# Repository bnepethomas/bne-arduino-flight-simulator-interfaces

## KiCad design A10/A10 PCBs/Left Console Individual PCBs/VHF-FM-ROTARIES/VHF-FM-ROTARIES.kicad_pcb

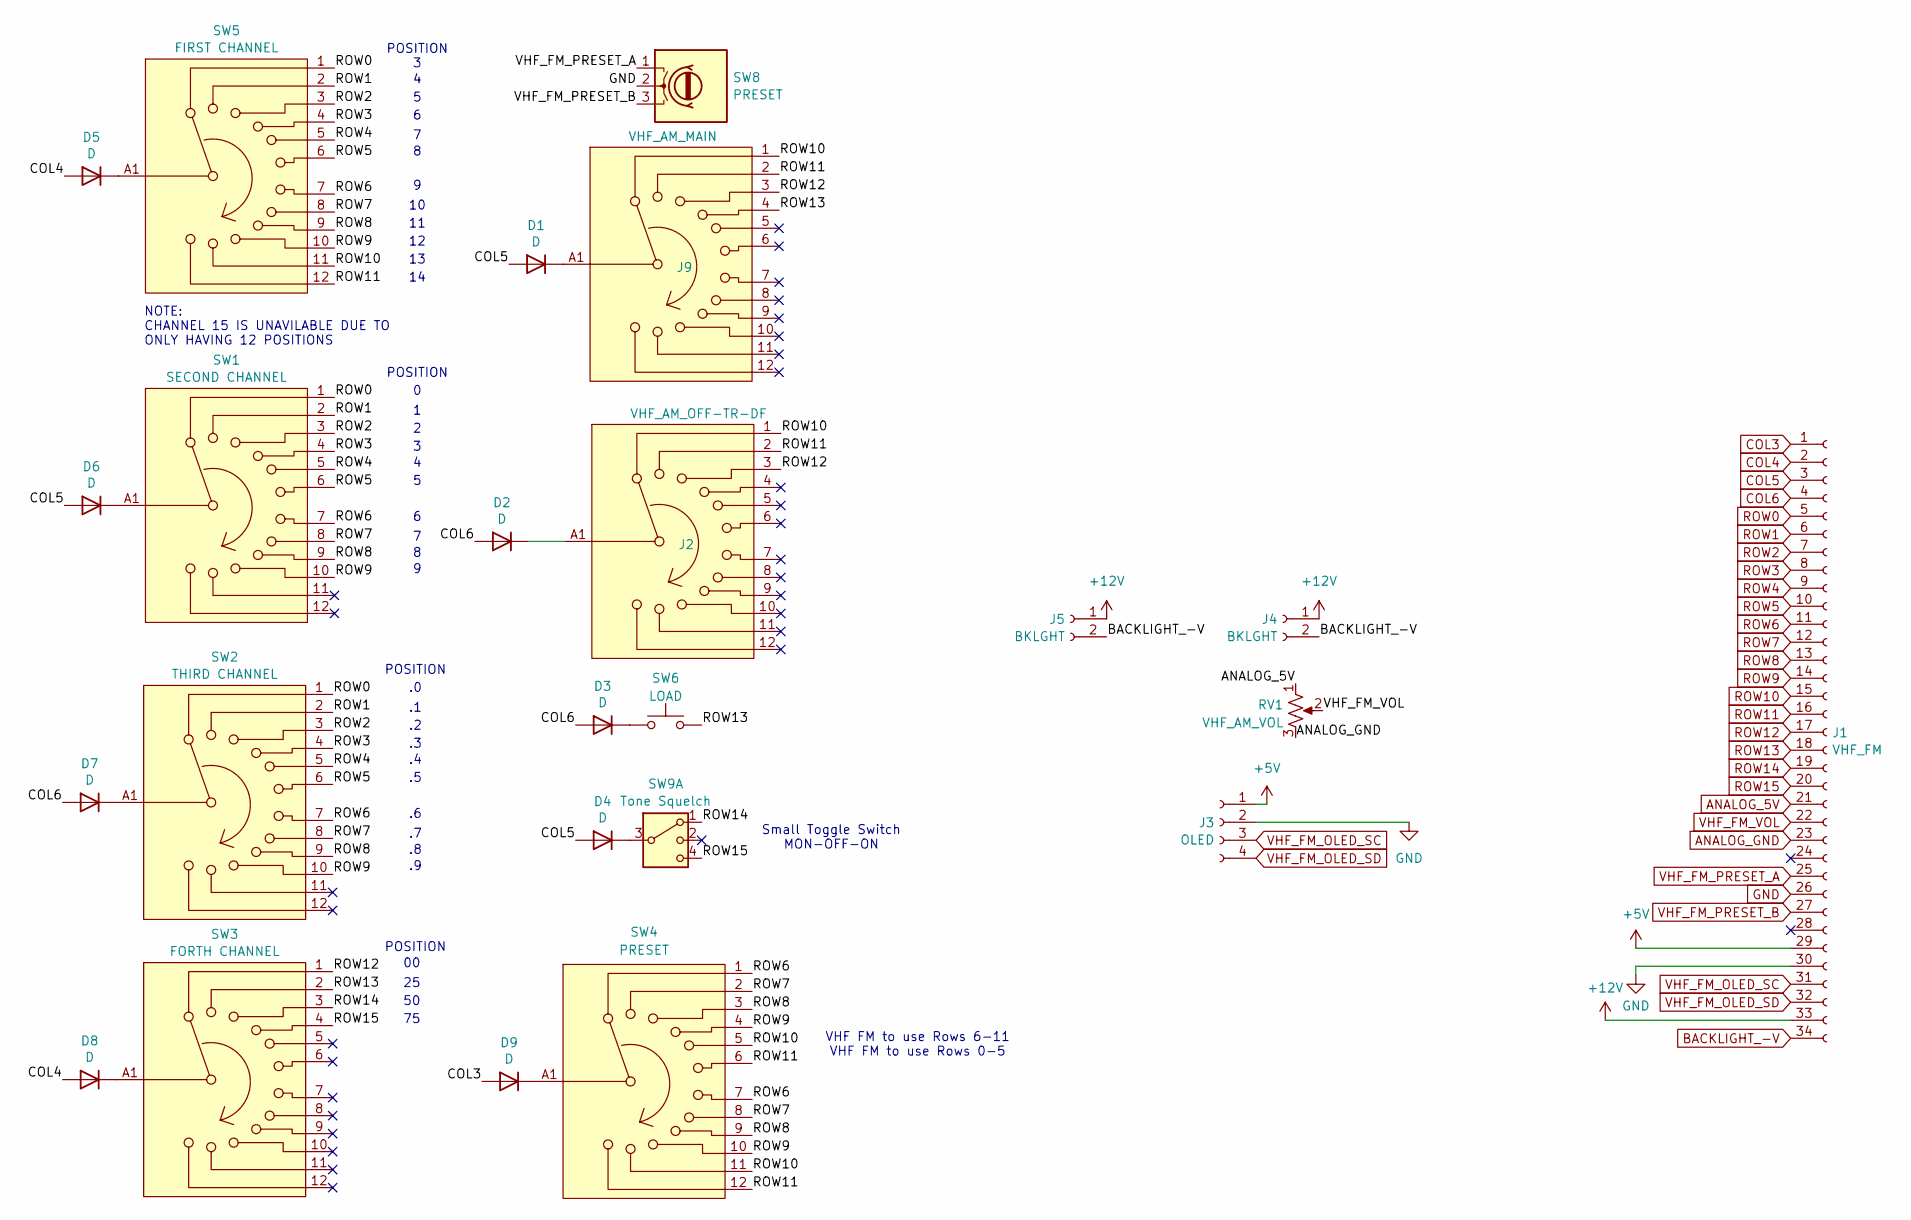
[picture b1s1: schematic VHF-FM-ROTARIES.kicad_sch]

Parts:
D1, D2, D3, D4, D5, D6, D7, D8, D9: D; D_A-405_P7.62mm_Horizontal
J1: VHF_FM; IDC-Header_2x17_P2.54mm_Vertical
J2: VHF_AM_OFF-TR-DF; ALPHA 12 POS
J3: OLED; JST_XH_B4B-XH-A_1x04_P2.50mm_Vertical
J4, J5: BKLGHT; JST_XH_B2B-XH-A_1x02_P2.50mm_Vertical
J9: VHF_AM_MAIN; ALPHA 12 POS
RV1: VHF_AM_VOL; JST_XH_B3B-XH-A_1x03_P2.50mm_Vertical
SW1: SECOND CHANNEL; ALPHA 12 POS
SW2: THIRD CHANNEL; ALPHA 12 POS
SW3: FORTH CHANNEL; ALPHA 12 POS
SW4: PRESET; ALPHA 12 POS
SW5: FIRST CHANNEL; ALPHA 12 POS
SW6: LOAD; JST_XH_B2B-XH-A_1x02_P2.50mm_Vertical
SW8: PRESET; JST_XH_B3B-XH-A_1x03_P2.50mm_Vertical
SW9: Tone Squelch; JST_XH_B3B-XH-A_1x03_P2.50mm_Vertical

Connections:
+5V: J1.29, J3.1
+12V: J1.33, J4.1, J5.1
ANALOG_5V: J1.21, RV1.1
ANALOG_GND: J1.23, RV1.3
BACKLIGHT_-V: J1.34, J4.2, J5.2
COL3: D9.2 (A), J1.1
COL4: D5.2 (A), D8.2 (A), J1.2
COL5: D1.2 (A), D4.2 (A), D6.2 (A), J1.3
COL6: D2.2 (A), D3.2 (A), D7.2 (A), J1.4
GND: J1.26, J1.30, J3.2, SW8.2
unnamed: D1.1 (K), J9.A1
unnamed: D2.1 (K), J2.A1
unnamed: D3.1 (K), SW6.1
unnamed: D4.1 (K), SW9.3
unnamed: D5.1 (K), SW5.A1
unnamed: D6.1 (K), SW1.A1
unnamed: D7.1 (K), SW2.A1
unnamed: D8.1 (K), SW3.A1
unnamed: D9.1 (K), SW4.A1
ROW0: J1.5, SW1.1, SW2.1, SW5.1
ROW1: J1.6, SW1.2, SW2.2, SW5.2
ROW2: J1.7, SW1.3, SW2.3, SW5.3
ROW3: J1.8, SW1.4, SW2.4, SW5.4
ROW4: J1.9, SW1.5, SW2.5, SW5.5
ROW5: J1.10, SW1.6, SW2.6, SW5.6
ROW6: J1.11, SW1.7, SW2.7, SW4.1, SW4.7, SW5.7
ROW7: J1.12, SW1.8, SW2.8, SW4.2, SW4.8, SW5.8
ROW8: J1.13, SW1.9, SW2.9, SW4.3, SW4.9, SW5.9
ROW9: J1.14, SW1.10, SW2.10, SW4.4, SW4.10, SW5.10
ROW10: J1.15, J2.1, J9.1, SW4.5, SW4.11, SW5.11
ROW11: J1.16, J2.2, J9.2, SW4.6, SW4.12, SW5.12
ROW12: J1.17, J2.3, J9.3, SW3.1
ROW13: J1.18, J9.4, SW3.2, SW6.2
ROW14: J1.19, SW3.3, SW9.1
ROW15: J1.20, SW3.4, SW9.4
VHF_FM_OLED_SC: J1.31, J3.3
VHF_FM_OLED_SD: J1.32, J3.4
VHF_FM_PRESET_A: J1.25, SW8.1
VHF_FM_PRESET_B: J1.27, SW8.3
VHF_FM_VOL: J1.22, RV1.2

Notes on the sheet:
VHF FM to use Rows 6-11 VHF FM to use Rows 0-5
NOTE: CHANNEL 15 IS UNAVILABLE DUE TO ONLY HAVING 12 POSITIONS
POSITION
Small Toggle Switch MON-OFF-ON

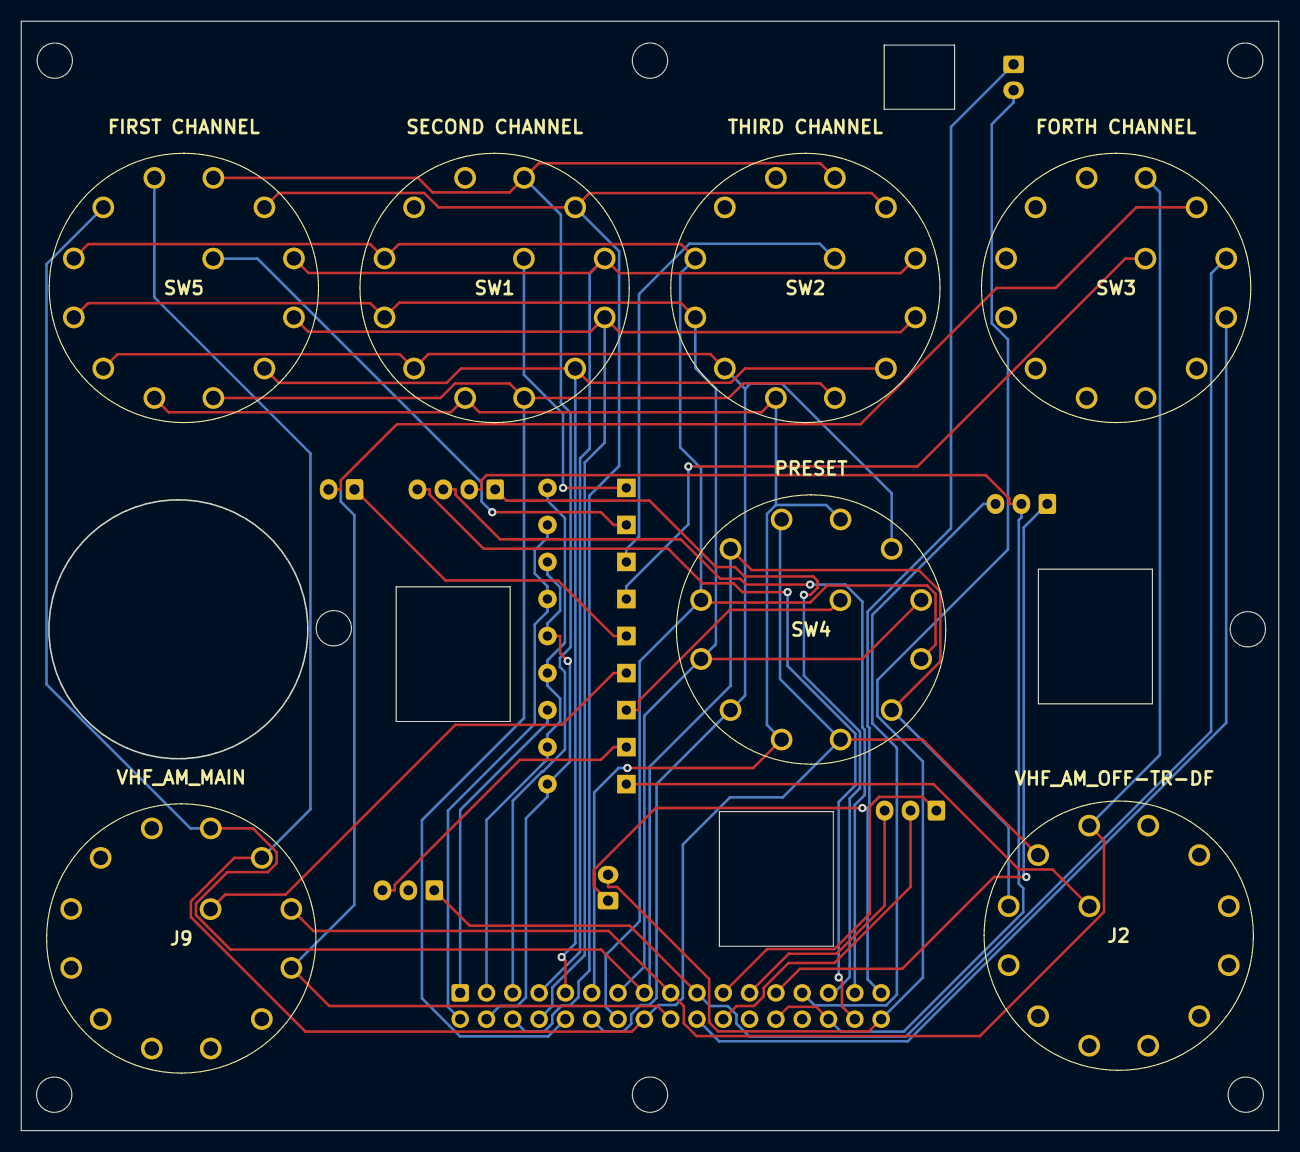
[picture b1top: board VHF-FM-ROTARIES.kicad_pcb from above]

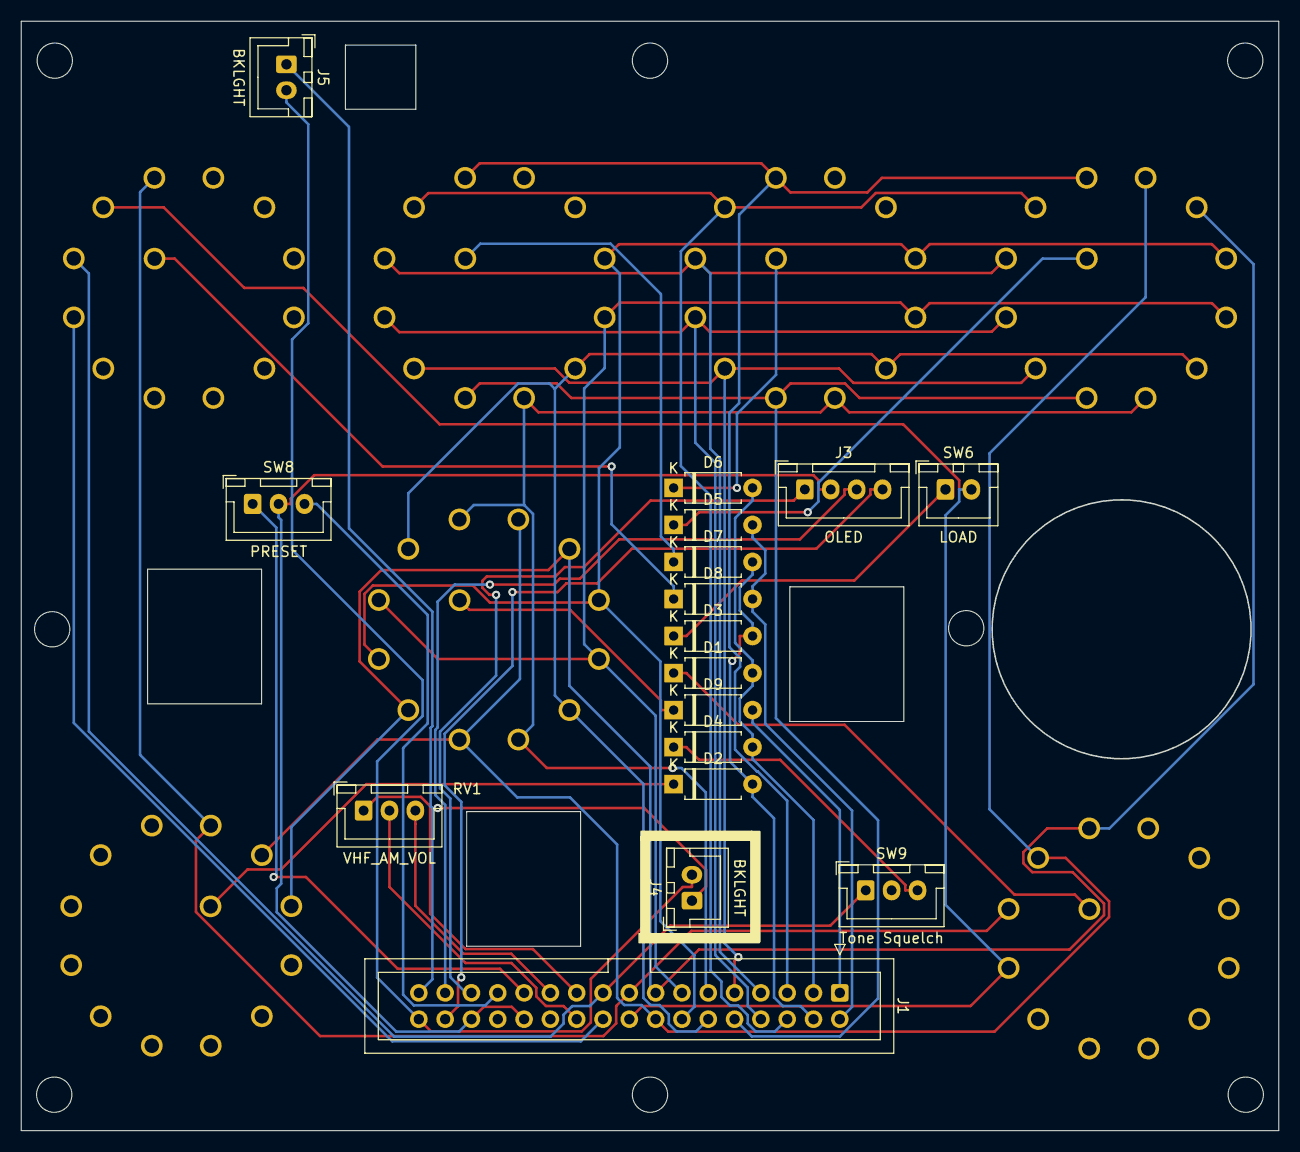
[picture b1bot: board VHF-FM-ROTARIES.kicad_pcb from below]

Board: 2 copper layers, 121.4 x 107.1 mm, 24 parts (17 on the bottom side), 40 nets.

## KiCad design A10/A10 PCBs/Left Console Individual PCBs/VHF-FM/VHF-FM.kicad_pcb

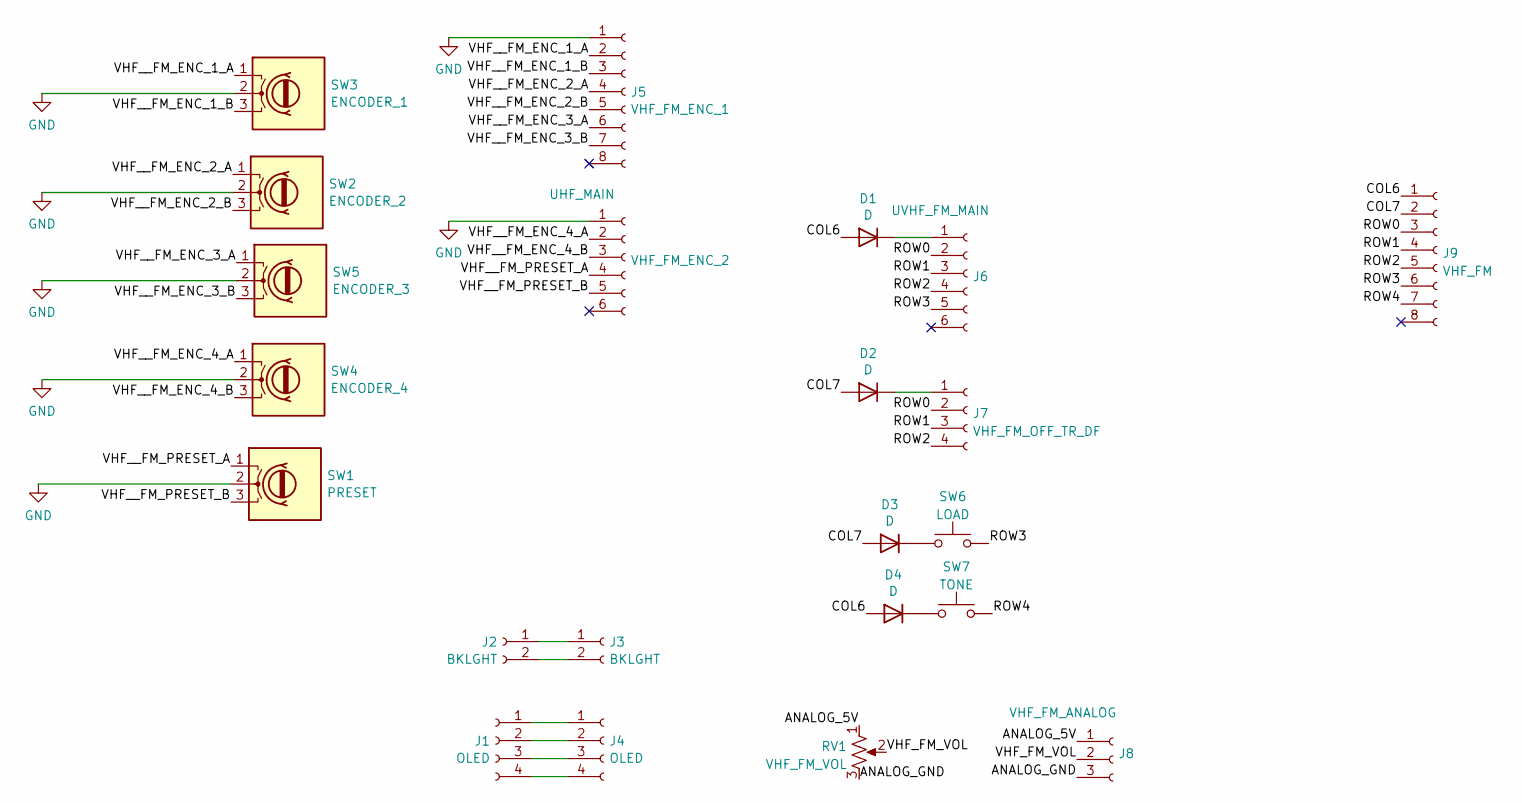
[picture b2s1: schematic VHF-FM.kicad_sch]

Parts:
D1, D2, D3, D4: D; D_A-405_P7.62mm_Horizontal
J1, J4: OLED; Molex_KK-254_AE-6410-04A_1x04_P2.54mm_Vertical
J2, J3: BKLGHT; Molex_KK-254_AE-6410-02A_1x02_P2.54mm_Vertical
J5: VHF_FM_ENC_1; Molex_KK-254_AE-6410-08A_1x08_P2.54mm_Vertical
J6: UVHF_FM_MAIN; Molex_KK-254_AE-6410-06A_1x06_P2.54mm_Vertical
J7: VHF_FM_OFF_TR_DF; Molex_KK-254_AE-6410-04A_1x04_P2.54mm_Vertical
J8: VHF_FM_ANALOG; Molex_KK-254_AE-6410-03A_1x03_P2.54mm_Vertical
J9: VHF_FM; Molex_KK-254_AE-6410-06A_1x06_P2.54mm_Vertical
RV1: VHF_FM_VOL; Molex_KK-254_AE-6410-03A_1x03_P2.54mm_Vertical
SW1: PRESET; Molex_KK-254_AE-6410-03A_1x03_P2.54mm_Vertical
SW2: ENCODER_2; Molex_KK-254_AE-6410-03A_1x03_P2.54mm_Vertical
SW3: ENCODER_1; Molex_KK-254_AE-6410-03A_1x03_P2.54mm_Vertical
SW4: ENCODER_4; Molex_KK-254_AE-6410-03A_1x03_P2.54mm_Vertical
SW5: ENCODER_3; Molex_KK-254_AE-6410-03A_1x03_P2.54mm_Vertical
SW6: LOAD; Molex_KK-254_AE-6410-02A_1x02_P2.54mm_Vertical
SW7: TONE; Molex_KK-254_AE-6410-02A_1x02_P2.54mm_Vertical
VHF_FM_ENC_2: UHF_MAIN; Molex_KK-254_AE-6410-06A_1x06_P2.54mm_Vertical

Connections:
/ANALOG_5V: J8.1, RV1.1
/ANALOG_GND: J8.3, RV1.3
/COL6: D1.2 (A), D4.2 (A), J9.1
/COL7: D2.2 (A), D3.2 (A), J9.2
/ROW0: J6.2, J7.2, J9.3
/ROW1: J6.3, J7.3, J9.4
/ROW2: J6.4, J7.4, J9.5
/ROW3: J6.5, J9.6, SW6.2
/ROW4: J9.7, SW7.2
/VHF_FM_VOL: J8.2, RV1.2
/VHF__FM_ENC_1_A: J5.2, SW3.1
/VHF__FM_ENC_1_B: J5.3, SW3.3
/VHF__FM_ENC_2_A: J5.4, SW2.1
/VHF__FM_ENC_2_B: J5.5, SW2.3
/VHF__FM_ENC_3_A: J5.6, SW5.1
/VHF__FM_ENC_3_B: J5.7, SW5.3
/VHF__FM_ENC_4_A: SW4.1, VHF_FM_ENC_2.2
/VHF__FM_ENC_4_B: SW4.3, VHF_FM_ENC_2.3
/VHF__FM_PRESET_A: SW1.1, VHF_FM_ENC_2.4
/VHF__FM_PRESET_B: SW1.3, VHF_FM_ENC_2.5
GND: J5.1, SW1.2, SW2.2, SW3.2, SW4.2, SW5.2, VHF_FM_ENC_2.1
unnamed: D1.1 (K), J6.1
unnamed: D2.1 (K), J7.1
unnamed: D3.1 (K), SW6.1
unnamed: D4.1 (K), SW7.1
unnamed: J1.1, J4.1
unnamed: J1.2, J4.2
unnamed: J1.3, J4.3
unnamed: J1.4, J4.4
unnamed: J2.1, J3.1
unnamed: J2.2, J3.2

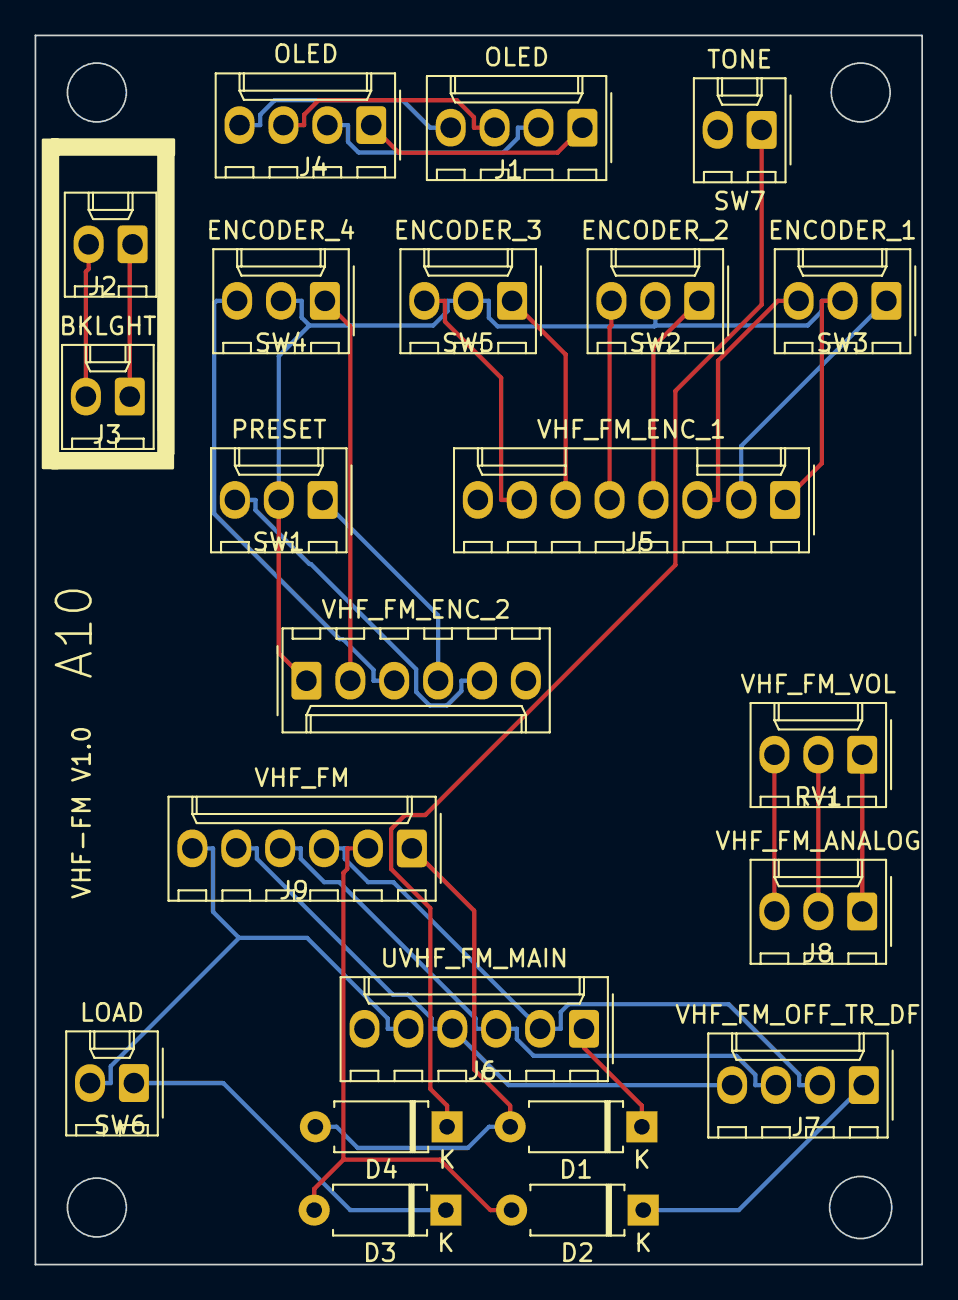
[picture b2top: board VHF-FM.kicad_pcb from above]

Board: 2 copper layers, 51.3 x 71.1 mm, 22 parts (0 on the bottom side), 30 nets.

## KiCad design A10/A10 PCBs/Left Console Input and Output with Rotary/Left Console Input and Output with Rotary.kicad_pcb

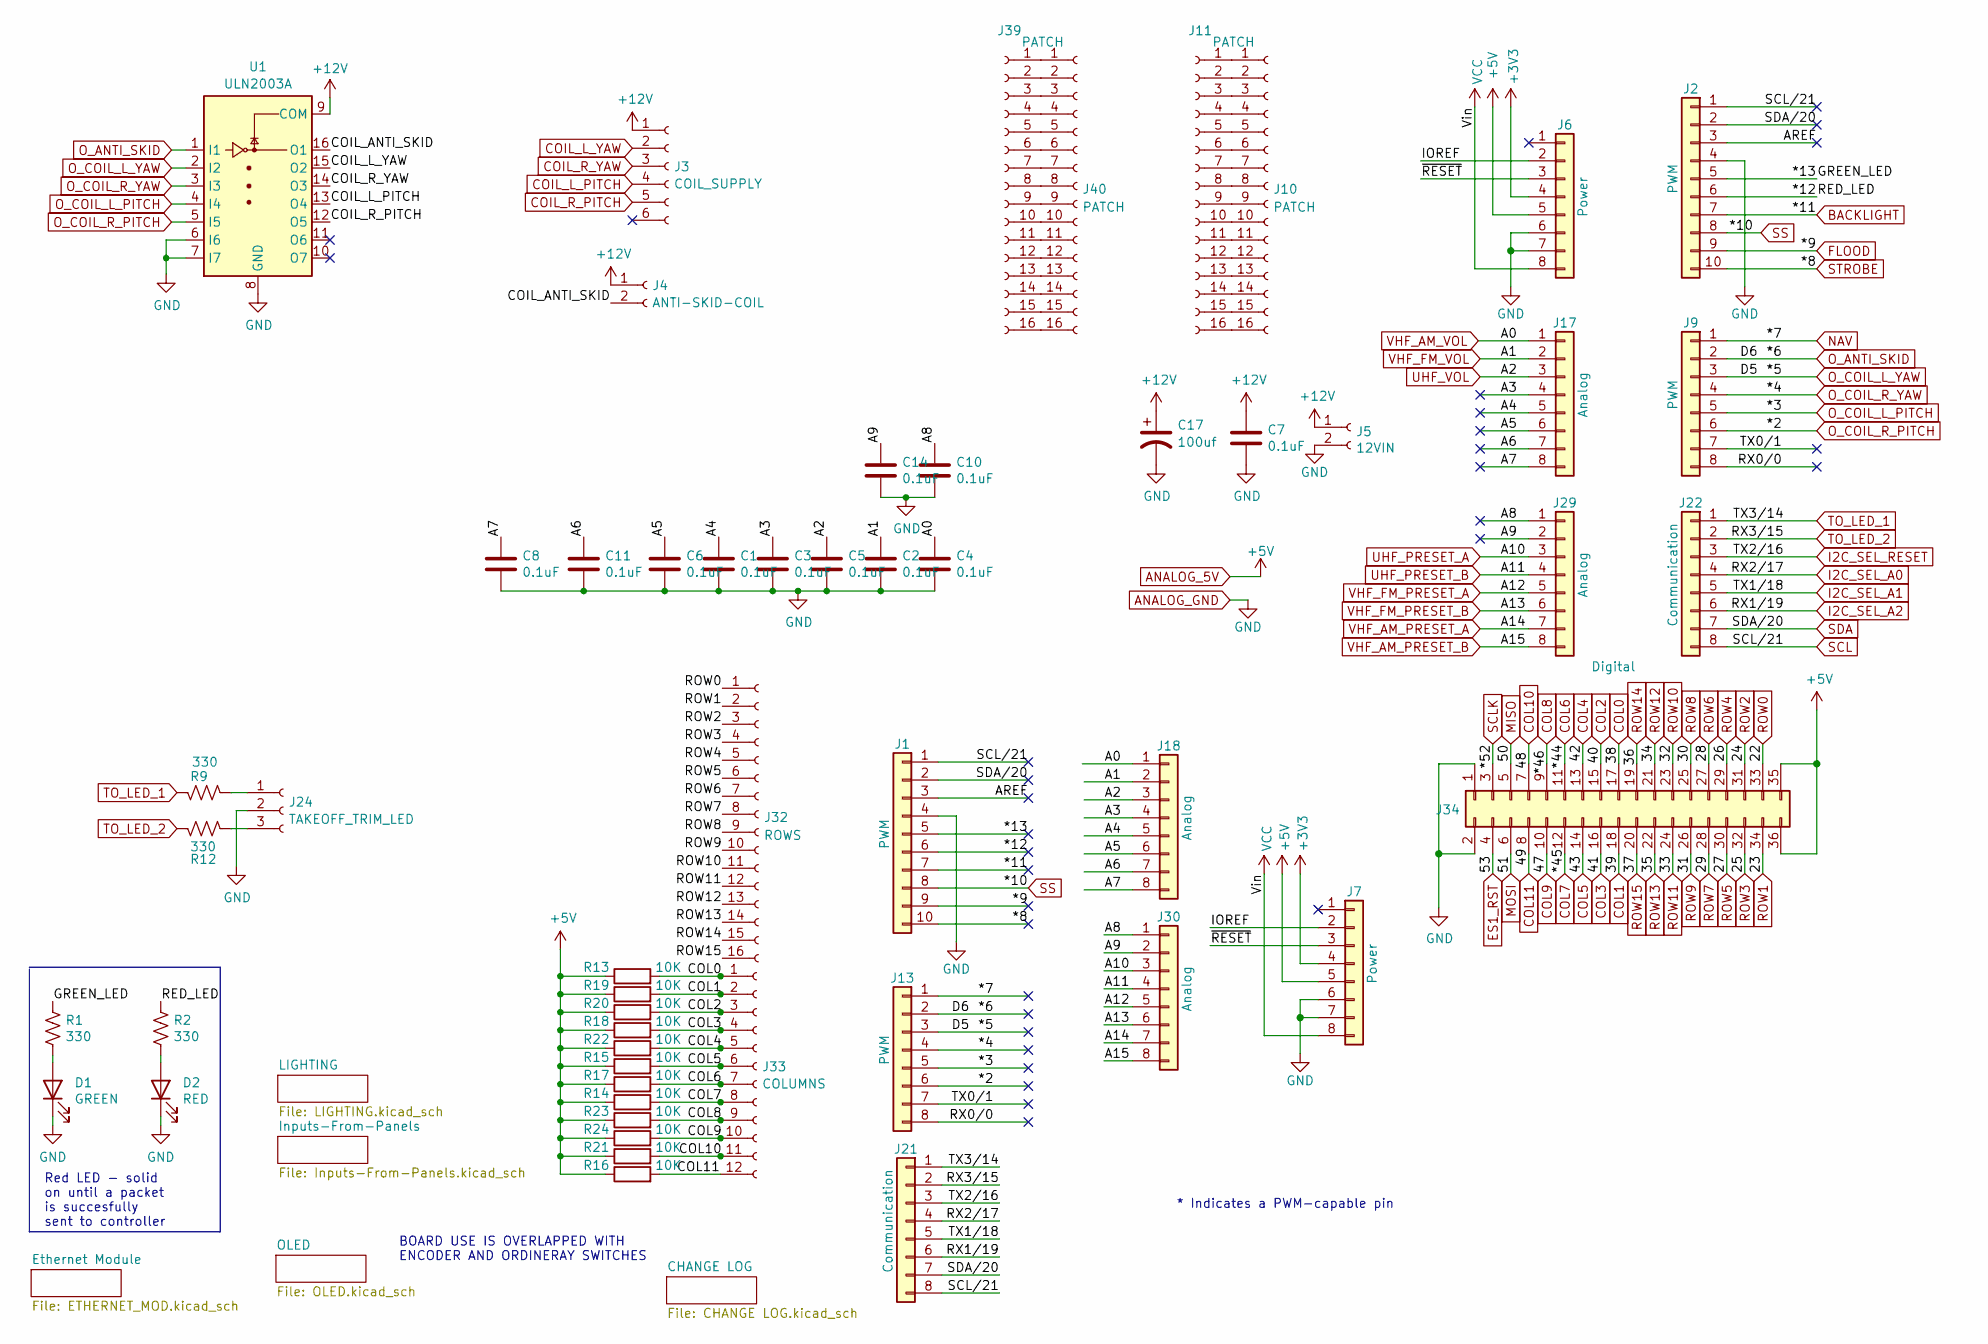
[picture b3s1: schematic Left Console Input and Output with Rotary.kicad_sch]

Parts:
C1, C2, C3, C4, C5, C6, C8, C10, C11, C14: 0.1uF; C_Disc_D6.0mm_W2.5mm_P5.00mm
C7: 0.1uF; C_Disc_D4.3mm_W1.9mm_P5.00mm
C17: 100uf; C_Radial_D6.3mm_H5.0mm_P2.50mm
D1: GREEN; LED_D3.0mm
D2: RED; LED_D3.0mm
J1, J2: PWM; PinSocket_1x10_P2.54mm_Vertical
J3: COIL_SUPPLY; Molex_KK-254_AE-6410-06A_1x06_P2.54mm_Vertical
J4: ANTI-SKID-COIL; Molex_KK-254_AE-6410-02A_1x02_P2.54mm_Vertical
J5: 12VIN; BarrelJack_Horizontal
J6, J7: Power; PinSocket_1x08_P2.54mm_Vertical
J9, J13: PWM; PinSocket_1x08_P2.54mm_Vertical
J10, J11, J39, J40: PATCH; PinHeader_1x16_P2.54mm_Vertical
J17, J18, J29, J30: Analog; PinSocket_1x08_P2.54mm_Vertical
J21, J22: Communication; PinSocket_1x08_P2.54mm_Vertical
J24: TAKEOFF_TRIM_LED; Molex_KK-254_AE-6410-03A_1x03_P2.54mm_Vertical
J32: ROWS; PinHeader_1x16_P2.54mm_Vertical
J33: COLUMNS; PinHeader_1x12_P2.54mm_Vertical
J34: Digital; PinSocket_2x18_P2.54mm_Vertical
R1, R2, R9, R12: 330; R_Axial_DIN0204_L3.6mm_D1.6mm_P2.54mm_Vertical
R13, R14, R15, R16, R17, R18, R19, R20, R21, R22, R23, R24: 10K; R_Axial_DIN0204_L3.6mm_D1.6mm_P2.54mm_Vertical
U1: ULN2003A; DIP-16_W7.62mm_LongPads

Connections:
+3V3: J6.4, J7.4; also elsewhere on the board
+12V: C7.1, C17.1, J3.1, J4.1, J5.1, U1.9 (COM); also elsewhere on the board
/*12: J1.6, J2.6, R2.1
/*13: J1.5, J2.5, R1.1
/A3: C3.1, J17.4, J18.4
/A4: C1.1, J17.5, J18.5
/A5: C6.1, J17.6, J18.6
/A6: C11.1, J17.7, J18.7
/A7: C8.1, J17.8, J18.8
/A8: C10.1, J29.1, J30.1
/A9: C14.1, J29.2, J30.2
/AREF: J1.3, J2.3
/COIL_ANTI_SKID: J4.2, U1.16 (O1)
/IOREF: J6.2, J7.2
/~RESET: J6.3, J7.3
BACKLIGHT: J1.7, J2.7; also elsewhere on the board
COIL_L_PITCH: J3.4, U1.13 (O4)
COIL_L_YAW: J3.2, U1.15 (O2)
COIL_R_PITCH: J3.5, U1.12 (O5)
COIL_R_YAW: J3.3, U1.14 (O3)
COL0: J33.1, J34.17, R13.2; also elsewhere on the board
COL1: J33.2, J34.18, R19.2; also elsewhere on the board
COL2: J33.3, J34.15, R20.2; also elsewhere on the board
COL3: J33.4, J34.16, R18.2; also elsewhere on the board
COL4: J33.5, J34.13, R22.2; also elsewhere on the board
COL5: J33.6, J34.14, R15.2; also elsewhere on the board
COL6: J33.7, J34.11, R17.2; also elsewhere on the board
COL7: J33.8, J34.12, R14.2; also elsewhere on the board
COL8: J33.9, J34.9, R23.2; also elsewhere on the board
COL9: J33.10, J34.10, R24.2; also elsewhere on the board
COL10: J33.11, J34.7, R21.2; also elsewhere on the board
COL11: J33.12, J34.8, R16.2; also elsewhere on the board
ES1_RST: J34.4; also elsewhere on the board
FLOOD: J1.9, J2.9; also elsewhere on the board
I2C_SEL_A0: J21.4, J22.4; also elsewhere on the board
I2C_SEL_A1: J21.5, J22.5; also elsewhere on the board
I2C_SEL_A2: J21.6, J22.6; also elsewhere on the board
I2C_SEL_RESET: J21.3, J22.3; also elsewhere on the board
MISO: J34.5; also elsewhere on the board
MOSI: J34.6; also elsewhere on the board
NAV: J9.1, J13.1; also elsewhere on the board
unnamed: D1.2 (A), R1.2
unnamed: D2.2 (A), R2.2
unnamed: J10.1, J11.1
unnamed: J10.2, J11.2
unnamed: J10.3, J11.3
unnamed: J10.4, J11.4
unnamed: J10.5, J11.5
unnamed: J10.6, J11.6
unnamed: J10.7, J11.7
unnamed: J10.8, J11.8
unnamed: J10.9, J11.9
unnamed: J10.10, J11.10
unnamed: J10.11, J11.11
unnamed: J10.12, J11.12
unnamed: J10.13, J11.13
unnamed: J10.14, J11.14
unnamed: J10.15, J11.15
unnamed: J10.16, J11.16
unnamed: J24.1, R9.1
unnamed: J24.3, R12.1
unnamed: J39.1, J40.1
unnamed: J39.2, J40.2
unnamed: J39.3, J40.3
unnamed: J39.4, J40.4
unnamed: J39.5, J40.5
unnamed: J39.6, J40.6
unnamed: J39.7, J40.7
unnamed: J39.8, J40.8
unnamed: J39.9, J40.9
unnamed: J39.10, J40.10
unnamed: J39.11, J40.11
unnamed: J39.12, J40.12
unnamed: J39.13, J40.13
unnamed: J39.14, J40.14
unnamed: J39.15, J40.15
unnamed: J39.16, J40.16
O_ANTI_SKID: J9.2, J13.2, U1.1 (I1)
O_COIL_L_PITCH: J9.5, J13.5, U1.4 (I4)
O_COIL_L_YAW: J9.3, J13.3, U1.2 (I2)
O_COIL_R_PITCH: J9.6, J13.6, U1.5 (I5)
O_COIL_R_YAW: J9.4, J13.4, U1.3 (I3)
ROW0: J32.1, J34.33; also elsewhere on the board
ROW1: J32.2, J34.34; also elsewhere on the board
ROW2: J32.3, J34.31; also elsewhere on the board
ROW3: J32.4, J34.32; also elsewhere on the board
ROW4: J32.5, J34.29; also elsewhere on the board
ROW5: J32.6, J34.30; also elsewhere on the board
ROW6: J32.7, J34.27; also elsewhere on the board
ROW7: J32.8, J34.28; also elsewhere on the board
ROW8: J32.9, J34.25; also elsewhere on the board
ROW9: J32.10, J34.26; also elsewhere on the board
ROW10: J32.11, J34.23; also elsewhere on the board
ROW11: J32.12, J34.24; also elsewhere on the board
ROW12: J32.13, J34.21; also elsewhere on the board
ROW13: J32.14, J34.22; also elsewhere on the board
ROW14: J32.15, J34.19; also elsewhere on the board
ROW15: J32.16, J34.20; also elsewhere on the board
SCL: J1.1, J2.1, J21.8, J22.8; also elsewhere on the board
SCLK: J34.3; also elsewhere on the board
SDA: J1.2, J2.2, J21.7, J22.7; also elsewhere on the board
SS: J1.8, J2.8; also elsewhere on the board
STROBE: J1.10, J2.10; also elsewhere on the board
UHF_PRESET_A: J29.3, J30.3; also elsewhere on the board
UHF_PRESET_B: J29.4, J30.4; also elsewhere on the board
UHF_VOL: C5.1, J17.3, J18.3; also elsewhere on the board
VCC: J6.8, J7.8
VHF_AM_PRESET_A: J29.7, J30.7; also elsewhere on the board
VHF_AM_PRESET_B: J29.8, J30.8; also elsewhere on the board
VHF_AM_VOL: C4.1, J17.1, J18.1; also elsewhere on the board
VHF_FM_PRESET_A: J29.5, J30.5; also elsewhere on the board
VHF_FM_PRESET_B: J29.6, J30.6; also elsewhere on the board
VHF_FM_VOL: C2.1, J17.2, J18.2; also elsewhere on the board

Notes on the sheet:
BOARD USE IS OVERLAPPED WITH ENCODER AND ORDINERAY SWITCHES
Red LED - solid on until a packet is succesfully sent to controller
* Indicates a PWM-capable pin

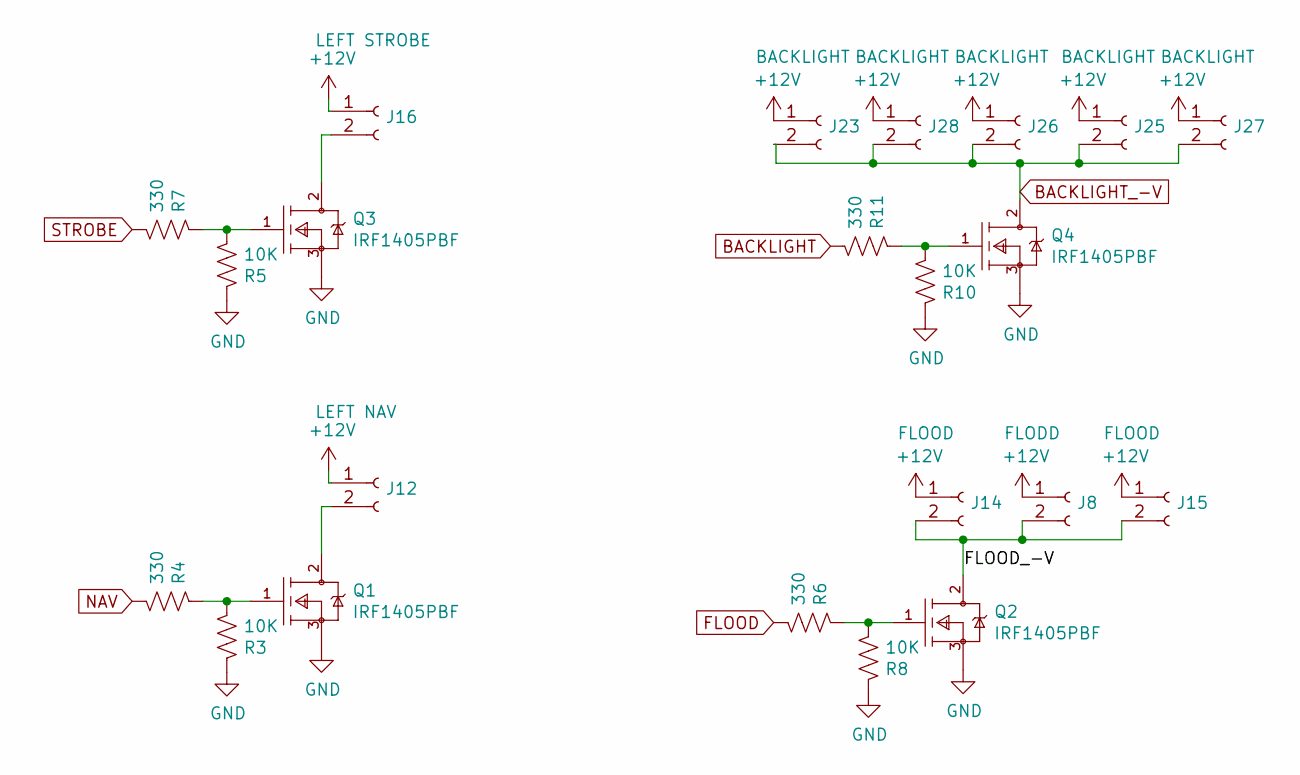
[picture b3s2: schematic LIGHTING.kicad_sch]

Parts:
J8: FLODD; Molex_KK-254_AE-6410-02A_1x02_P2.54mm_Vertical
J12: LEFT NAV; Molex_KK-254_AE-6410-02A_1x02_P2.54mm_Vertical
J14, J15: FLOOD; Molex_KK-254_AE-6410-02A_1x02_P2.54mm_Vertical
J16: LEFT STROBE; Molex_KK-254_AE-6410-02A_1x02_P2.54mm_Vertical
J23, J25, J26, J27, J28: BACKLIGHT; Molex_KK-254_AE-6410-02A_1x02_P2.54mm_Vertical
Q1, Q2, Q3, Q4: IRF1405PBF; TO-220-3_Vertical; mouser part number 942-IRF1405PBF; digikey description MOSFET N-CH 55V 169A TO-220AB
R3, R5, R8, R10: 10K; R_Axial_DIN0204_L3.6mm_D1.6mm_P2.54mm_Vertical
R4, R6, R7, R11: 330; R_Axial_DIN0204_L3.6mm_D1.6mm_P2.54mm_Vertical

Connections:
+12V: J8.1, J12.1, J14.1, J15.1, J16.1, J23.1, J25.1, J26.1, J27.1, J28.1; also elsewhere on the board
/LIGHTING/FLOOD_-V: J8.2, J14.2, J15.2, Q2.2 (D)
BACKLIGHT: R11.2; also elsewhere on the board
BACKLIGHT_-V: J23.2, J25.2, J26.2, J27.2, J28.2, Q4.2 (D); also elsewhere on the board
FLOOD: R6.2; also elsewhere on the board
NAV: R4.2; also elsewhere on the board
unnamed: J12.2, Q1.2 (D)
unnamed: J16.2, Q3.2 (D)
unnamed: Q1.1 (G), R3.2, R4.1
unnamed: Q2.1 (G), R6.1, R8.2
unnamed: Q3.1 (G), R5.2, R7.1
unnamed: Q4.1 (G), R10.2, R11.1
STROBE: R7.2; also elsewhere on the board

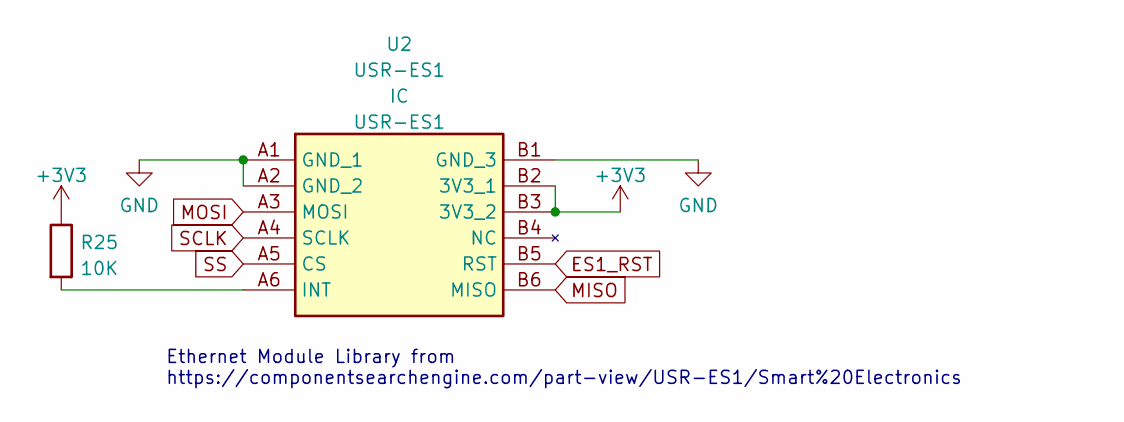
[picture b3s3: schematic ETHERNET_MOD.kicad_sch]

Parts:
R25: 10K; R_Axial_DIN0204_L3.6mm_D1.6mm_P2.54mm_Vertical
U2: USR-ES1; USRES1; Manufacturer_Part_Number USR-ES1

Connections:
+3V3: R25.1, U2.B2 (3V3_1), U2.B3 (3V3_2); also elsewhere on the board
ES1_RST: U2.B5 (RST); also elsewhere on the board
MISO: U2.B6 (MISO); also elsewhere on the board
MOSI: U2.A3 (MOSI); also elsewhere on the board
unnamed: R25.2, U2.A6 (INT)
SCLK: U2.A4 (SCLK); also elsewhere on the board
SS: U2.A5 (CS); also elsewhere on the board

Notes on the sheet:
Ethernet Module Library from https://componentsearchengine.com/part-view/USR-ES1/Smart%20Electronics

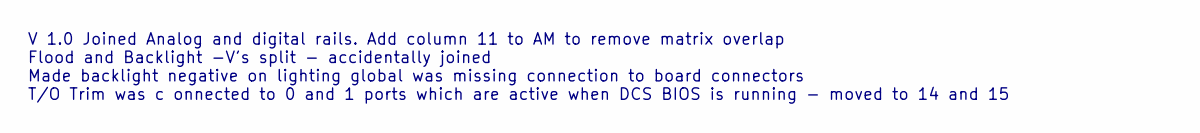
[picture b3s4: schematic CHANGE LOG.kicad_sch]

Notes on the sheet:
V 1.0 Joined Analog and digital rails. Add column 11 to AM to remove matrix overlap Flood and Backlight -V's split - accidentally joined Made backlight negative on lighting global was missing connection to board connectors T/O Trim was c onnected to 0 and 1 ports which are active when DCS BIOS is r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

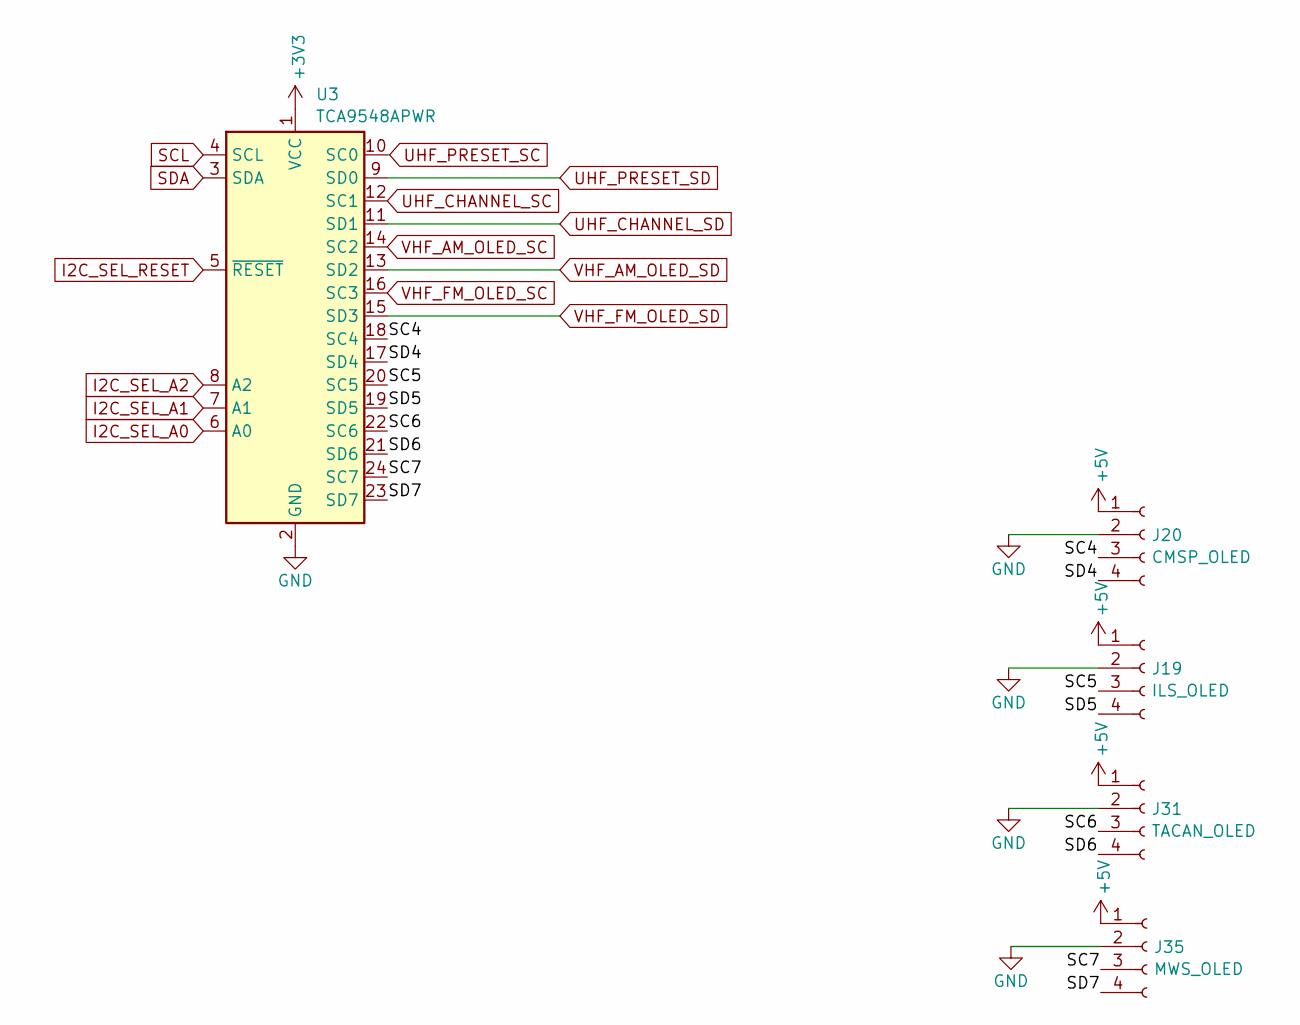
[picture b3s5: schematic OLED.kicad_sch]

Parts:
J19: ILS_OLED; PinSocket_1x04_P2.54mm_Vertical
J20: CMSP_OLED; PinSocket_1x04_P2.54mm_Vertical
J31: TACAN_OLED; PinSocket_1x04_P2.54mm_Vertical
J35: MWS_OLED; PinSocket_1x04_P2.54mm_Vertical
U3: TCA9548APWR; DIP-24_TCA9548A

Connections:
+3V3: U3.1 (VCC); also elsewhere on the board
/OLED/SC4: J20.3, U3.18 (SC4)
/OLED/SC5: J19.3, U3.20 (SC5)
/OLED/SC6: J31.3, U3.22 (SC6)
/OLED/SC7: J35.3, U3.24 (SC7)
/OLED/SD4: J20.4, U3.17 (SD4)
/OLED/SD5: J19.4, U3.19 (SD5)
/OLED/SD6: J31.4, U3.21 (SD6)
/OLED/SD7: J35.4, U3.23 (SD7)
I2C_SEL_A0: U3.6 (A0); also elsewhere on the board
I2C_SEL_A1: U3.7 (A1); also elsewhere on the board
I2C_SEL_A2: U3.8 (A2); also elsewhere on the board
I2C_SEL_RESET: U3.5 (~RESET); also elsewhere on the board
SCL: U3.4 (SCL); also elsewhere on the board
SDA: U3.3 (SDA); also elsewhere on the board
UHF_CHANNEL_SC: U3.12 (SC1); also elsewhere on the board
UHF_CHANNEL_SD: U3.11 (SD1); also elsewhere on the board
UHF_PRESET_SC: U3.10 (SC0); also elsewhere on the board
UHF_PRESET_SD: U3.9 (SD0); also elsewhere on the board
VHF_AM_OLED_SC: U3.14 (SC2); also elsewhere on the board
VHF_AM_OLED_SD: U3.13 (SD2); also elsewhere on the board
VHF_FM_OLED_SC: U3.16 (SC3); also elsewhere on the board
VHF_FM_OLED_SD: U3.15 (SD3); also elsewhere on the board
